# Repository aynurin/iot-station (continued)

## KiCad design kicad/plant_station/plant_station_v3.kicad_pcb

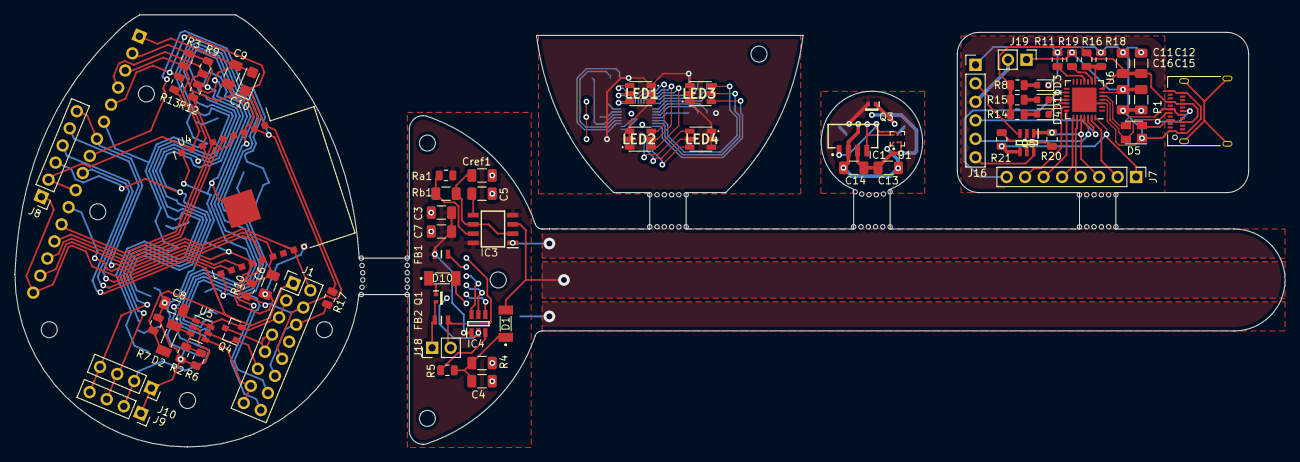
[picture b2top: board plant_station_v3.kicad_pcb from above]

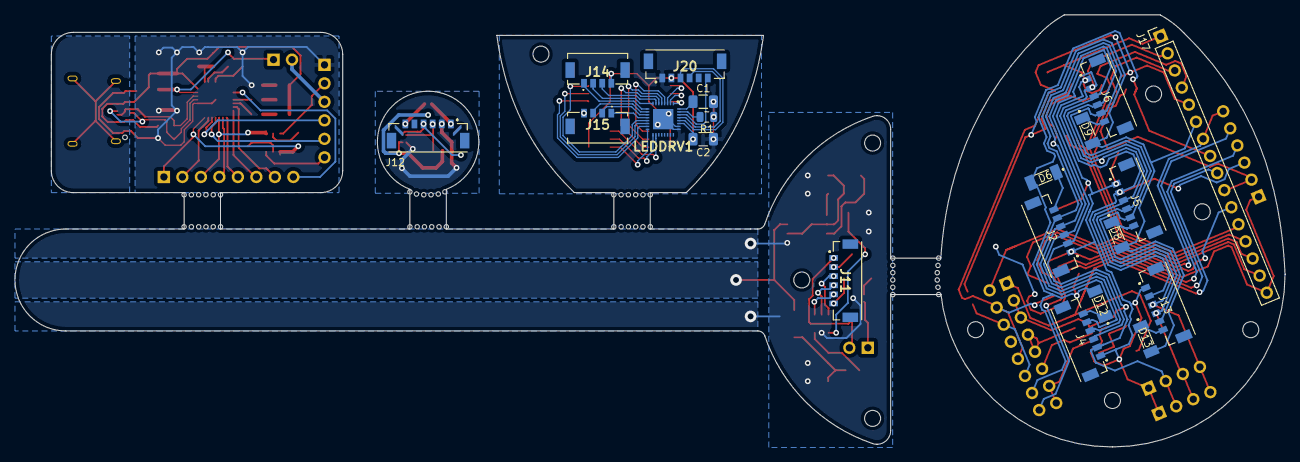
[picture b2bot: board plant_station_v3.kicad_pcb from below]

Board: 2 copper layers, 174.4 x 59.3 mm, 90 parts (20 on the bottom side), 95 nets.

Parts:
C1, C2, C4: 1μF; C_1206_3216Metric
C3, C6, C9, C11, C14, C15: 0.1μF; C_1206_3216Metric
C5: 10nF; C_1206_3216Metric
C7, C12, C13, C16: 4.7uF; C_1206_3216Metric
C8: 0.1uF; C_1206_3216Metric
C10: 220uF; CP_EIA-3216-18_Kemet-A
Cref1: 470pF; C_1206_3216Metric
D1, D2, D6, D8, D9, D10, D12, D13: LS4148; MELF_SOD_80_3_BZT55B13GS08
D3: 150060AS75000; LED_0603_1608Metric
D4: 150060BS75020; LED_0603_1608Metric
D5: SP0503BAHT; SOT-143
D11: 150060VS75000; LED_0603_1608Metric
FB1, FB2: BLM21AG601SZ1D; Ferrite_Bead_0805_BLM21
IC1: VEML7700-TT; VEML7700
IC3: TLC555CDR; SOIC127P600X175-8N
IC4: ADC081C021CIMK_NOPB; SOT95P280X110-6N
J1: Conn_02x08_Odd_Even; PinHeader_2x08_P2.54mm_Vertical
J2, J4, J5, J6, J13: MB_I2C; Molex_Conn_SMD_01x06_505567_0671
J7: Conn_01x08; PinHeader_1x08_P2.54mm_Vertical
J8: UART; PinHeader_1x06_P2.54mm_Vertical
J9: I2C SCREEN; PinSocket_1x04_P2.54mm_Vertical
J10: I2C HOST; PinSocket_1x04_P2.54mm_Vertical
J11: SOIL_I2C; Molex_Conn_SMD_01x06_505567_0671
J12: WEATHER_I2C; Molex_Conn_SMD_01x06_505567_0671
J14: Ambient_Led_6; Molex_Conn_SMD_01x04_505567_0471
J15: Ambient_Led_5; Molex_Conn_SMD_01x04_505567_0471
J16: Conn_01x06; PinHeader_1x06_P2.54mm_Vertical
J17: GPIO; PinHeader_1x16_P2.54mm_Vertical
J18: ALWAYS_ON; PinHeader_1x02_P2.54mm_Vertical
J19: Ammeter_Jumper; PinHeader_1x02_P2.54mm_Vertical
J20: LED_I2C; Molex_Conn_SMD_01x06_505567_0671
LED1, LED2, LED3, LED4: KRTBLSLPS1.32-VUVX-EQ+BTBV-D8+TWTZ-L1-B; KRTBLSLPS132VUVXEQBTBVD8TWTZL1B
LEDDRV1: LP5024RSMR; QFN40P400X400X100-33N-D
P1: USB_C_Plug_USB2.0; USB_C_Receptacle_Amphenol_12401610E4-2A
Q1, Q3: DTC113Z; DTC113ZEBTL
Q4: DMG2301L; SOT-23
Q5: BC817DS,115; SOT95P275X110-6N
R1: 4K9; R_0805_2012Metric
R2: 16.9K; R_0805_2012Metric
R3, R9: 4K7; R_0805_2012Metric
R4: 1M; R_1206_3216Metric
R5: 22; R_0805_2012Metric
R6: 97.6K; R_0805_2012Metric
R7, R10, R11, R12, R13, R17, R20, R21: 10K; R_0805_2012Metric
R8, R14, R15, R19: 1K; R_0805_2012Metric
R16: 22K1; R_0805_2012Metric
R18: 47K5; R_0805_2012Metric
Ra1: 330; R_0805_2012Metric
Rb1: 1K6; R_1206_3216Metric
U1: HDC2010YPAT; BGA6C100X50P2X3_146X146X67
U4: ESP-WROOM-02
U5: TPL5110; SOT-23-6
U6: CP2102N-A01-GQFN28; QFN-28-1EP_5x5mm_P0.5mm_EP3.35x3.35mm

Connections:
+3V3: C10.1, J1.4, J1.10, J17.5, R10.1, R13.1, U4.1
/ALL_EN: D6.2, D8.2, D9.2, D12.2, D13.2, J1.14, J17.6, U4.10
/HOST_WAKE: J2.5, J4.5, J5.5, J6.5, J13.5
/SCL: J2.4, J4.4, J5.4, J6.4, J9.3, J10.3, J13.4, J17.4, R9.2, U4.3
/SDA: J2.3, J4.3, J5.3, J6.3, J9.4, J10.4, J13.3, J17.3, R3.2, U4.7
/env_sensor/ALL_EN: J12.6, Q3.1
/env_sensor/GNDA: C13.2, C14.2, IC1.3, Q3.3, U1.B1, U1.C1
/env_sensor/SCL: IC1.1, J12.4, U1.B2
/env_sensor/SDA: IC1.4, J12.3, U1.A2
/esp8266/ESP_EN: C9.2, J17.8, R17.1, U4.2
/esp8266/ESP_RST: C6.2, J8.6, J17.7, R10.2, U4.15
/esp8266/GPIO0: J8.2, J17.10, R13.2, U4.8
/esp8266/GPIO5: J1.16, J17.11, U4.14
/esp8266/GPIO12: J17.14, U4.4
/esp8266/GPIO13: J17.13, U4.5
/esp8266/GPIO15: J17.12, R12.2, U4.6
/esp8266/GPIO16: J1.2, J17.15, U4.17
/esp8266/USB_RXD: J8.5, U4.12
/esp8266/USB_TXD: J8.4, U4.11
/esp8266/WAKE_UP: D2.2, J1.1, J17.9, R7.2
/leds/ALL_EN: J20.6, LEDDRV1.30
/leds/LED_1_B: LED1.C1, LEDDRV1.3
/leds/LED_1_G: LED1.C2, LEDDRV1.2
/leds/LED_1_R: LED1.C3, LEDDRV1.1
/leds/LED_2_B: LED2.C1, LEDDRV1.6
/leds/LED_2_G: LED2.C2, LEDDRV1.5
/leds/LED_2_R: LED2.C3, LEDDRV1.4
/leds/LED_3_B: J14.1, LEDDRV1.9
/leds/LED_3_G: J14.2, LEDDRV1.8
/leds/LED_3_R: J14.3, LEDDRV1.7
/leds/LED_4_B: J15.1, LEDDRV1.12
/leds/LED_4_G: J15.2, LEDDRV1.11
/leds/LED_4_R: J15.3, LEDDRV1.10
/leds/LED_5_B: LED3.C1, LEDDRV1.15
/leds/LED_5_G: LED3.C2, LEDDRV1.14
/leds/LED_5_R: LED3.C3, LEDDRV1.13
/leds/LED_6_B: LED4.C1, LEDDRV1.18
/leds/LED_6_G: LED4.C2, LEDDRV1.17
/leds/LED_6_R: LED4.C3, LEDDRV1.16
/leds/SCL: J20.4, LEDDRV1.29
/leds/SDA: J20.3, LEDDRV1.28
/moisture_sensor/ALL_EN: D10.2, J11.6
/moisture_sensor/GNDA: C3.1, C4.2, C5.2, C7.2, Cref1.2, IC3.1, IC4.2, Q1.3, R4.2
/moisture_sensor/HOST_WAKE: IC4.4, J11.5
/moisture_sensor/SCL: IC4.5, J11.4
/moisture_sensor/SDA: IC4.6, J11.3
/moisture_sensor/Sensor_Inside: D1.2, IC3.3
/moisture_sensor/VA: C3.2, C7.1, FB1.2, IC3.4, IC3.8, IC4.1, Ra1.1
/usb_serial/D+: D5.4, P1.A6, P1.B6, U6.4
/usb_serial/D-: D5.3, P1.A7, P1.B7, U6.5
/usb_serial/ESP_RST: J16.6, Q5.6
/usb_serial/GPIO0: J16.2, Q5.3
/usb_serial/USB_CTS: J7.4, U6.23
/usb_serial/USB_DSR: J7.2, U6.27
/usb_serial/USB_DTR: J7.1, Q5.4, R21.1, U6.28
/usb_serial/USB_GPIO.4: J7.5, U6.22
/usb_serial/USB_GPIO.5: J7.6, U6.21
/usb_serial/USB_GPIO.6: J7.7, U6.20
/usb_serial/USB_RTS: J7.3, Q5.1, R20.2, U6.24
/usb_serial/USB_RXD: J16.5, U6.25
/usb_serial/USB_RXT: D11.1, U6.18
/usb_serial/USB_TXD: J16.4, U6.26
/usb_serial/USB_TXT: D4.1, U6.19
/usb_serial/USB_WAKEUP: J7.8, U6.16
GND: C1.2, C2.1, C6.1, C8.1, C9.1, C10.2, C11.2, C12.1, C15.2, C16.1, D3.1, D5.1, FB2.2, J2.1, J4.1, J5.1, J6.1, J8.1, J9.1, J10.1, J11.1, J12.1, J13.1, J16.1, J17.1, J17.16, J18.2, J20.1, LEDDRV1.25, LEDDRV1.26, LEDDRV1.33, P1.A1, P1.A12, P1.B1, P1.B12, Q3.2, R1.1, R2.2, R6.2, R7.1, R11.2, R12.1, R18.2, U4.9, U4.13, U4.18, U4.19, U5.2, U6.3, U6.29
unnamed: C1.1, LEDDRV1.32
unnamed: C4.1, D1.1, R4.1, R5.2
unnamed: C5.1, IC3.5
unnamed: C11.1, C12.2, D5.2, P1.A4, P1.A9, P1.B4, P1.B9, R8.1, R14.1, R15.1, R16.2, U6.7
unnamed: C15.1, C16.2, J19.1, R19.1, U6.6
unnamed: Cref1.1, IC3.2, IC3.6, Rb1.2
unnamed: D2.1, R2.1, R6.1, U5.3
unnamed: D3.2, R8.2
unnamed: D4.2, R14.2
unnamed: D6.1, J2.6
unnamed: D8.1, J5.6
unnamed: D9.1, J6.6
unnamed: D10.1, Q1.1
unnamed: D11.2, R15.2
unnamed: D12.1, J4.6
unnamed: D13.1, J13.6
unnamed: FB2.1, J18.1, Q1.2
unnamed: IC3.7, Ra1.2, Rb1.1
unnamed: IC4.3, R5.1
unnamed: J1.7, J1.9, Q4.3
unnamed: J1.11, Q4.1, U5.5
unnamed: J1.6, J1.12, R17.2
unnamed: J1.13, J1.15, U5.4
unnamed: LEDDRV1.31, R1.2
unnamed: Q5.2, R21.2
unnamed: Q5.5, R20.1
unnamed: R11.1, U6.11
unnamed: R16.1, R18.1, U6.8
unnamed: R19.2, U6.9
VDD: C2.2, C8.2, C13.1, C14.1, FB1.1, IC1.2, J1.3, J1.5, J2.2, J4.2, J5.2, J6.2, J8.3, J9.2, J10.2, J11.2, J12.2, J13.2, J14.4, J15.4, J16.3, J17.2, J19.2, J20.2, LED1.A1, LED1.A2, LED1.A3, LED2.A1, LED2.A2, LED2.A3, LED3.A1, LED3.A2, LED3.A3, LED4.A1, LED4.A2, LED4.A3, LEDDRV1.27, Q4.2, R3.1, R9.1, U1.A1, U5.1, U5.6

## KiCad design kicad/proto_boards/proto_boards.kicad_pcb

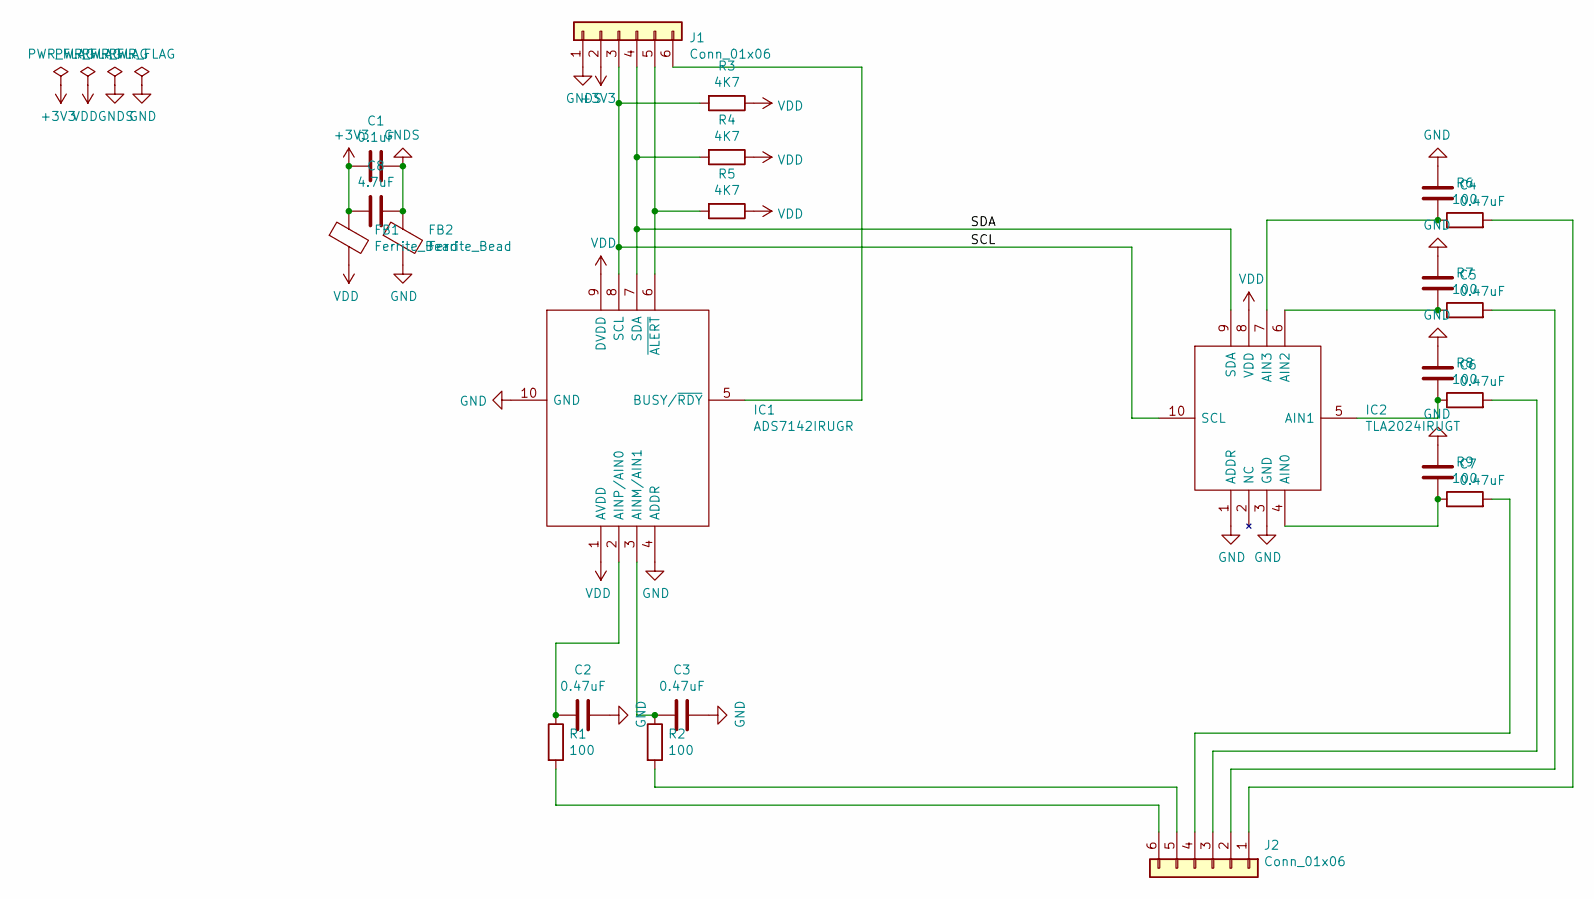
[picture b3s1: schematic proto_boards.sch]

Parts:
C1: 0.1uF; C_1206_3216Metric
C2, C3, C4, C5, C6, C7: 0.47uF; C_0805_2012Metric
C8: 4.7uF; C_1206_3216Metric
FB1, FB2: Ferrite_Bead; C_0805_2012Metric
IC1: ADS7142IRUGR; ADS1018IRUGT; Manufacturer_Part_Number ADS7142IRUGR; Mouser Part Number 595-ADS7142IRUGR
IC2: TLA2024IRUGT; ADS1018IRUGT; Manufacturer_Part_Number TLA2024IRUGT; Mouser Part Number 595-TLA2024IRUGT
J1, J2: Conn_01x06; PinHeader_1x06_P2.54mm_Vertical
R1, R2, R6, R7, R8, R9: 100; R_1206_3216Metric
R3, R4, R5: 4K7; R_0805_2012Metric

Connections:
+3V3: C1.2, C8.2, FB1.1, J1.2
/SCL: IC1.8 (SCL), IC2.10 (SCL), J1.3, R3.2
/SDA: IC1.7 (SDA), IC2.9 (SDA), J1.4, R4.2
GND: C2.1, C3.1, C4.1, C5.1, C6.1, C7.1, FB2.2, IC1.4 (ADDR), IC1.10 (GND), IC2.1 (ADDR), IC2.3 (GND)
GNDS: C1.1, C8.1, FB2.1, J1.1
unnamed: C2.2, IC1.2 (AINP/AIN0), R1.1
unnamed: C3.2, IC1.3 (AINM/AIN1), R2.1
unnamed: C4.2, IC2.7 (AIN3), R6.1
unnamed: C5.2, IC2.6 (AIN2), R7.1
unnamed: C6.2, IC2.5 (AIN1), R8.1
unnamed: C7.2, IC2.4 (AIN0), R9.1
unnamed: IC1.5 (BUSY/~RDY), J1.6
unnamed: IC1.6 (~ALERT), J1.5, R5.2
unnamed: J2.1, R6.2
unnamed: J2.2, R7.2
unnamed: J2.3, R8.2
unnamed: J2.4, R9.2
unnamed: J2.5, R2.2
unnamed: J2.6, R1.2
VDD: FB1.2, IC1.1 (AVDD), IC1.9 (DVDD), IC2.8 (VDD), R3.1, R4.1, R5.1

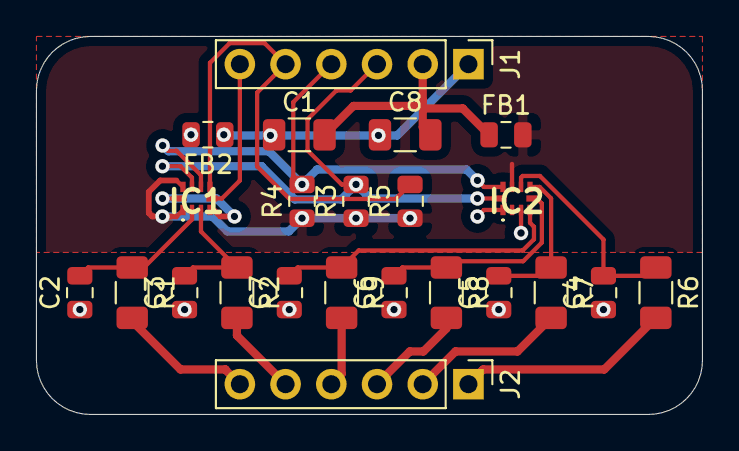
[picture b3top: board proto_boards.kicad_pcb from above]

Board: 2 copper layers, 37.0 x 21.0 mm, 23 parts (0 on the bottom side), 20 nets.

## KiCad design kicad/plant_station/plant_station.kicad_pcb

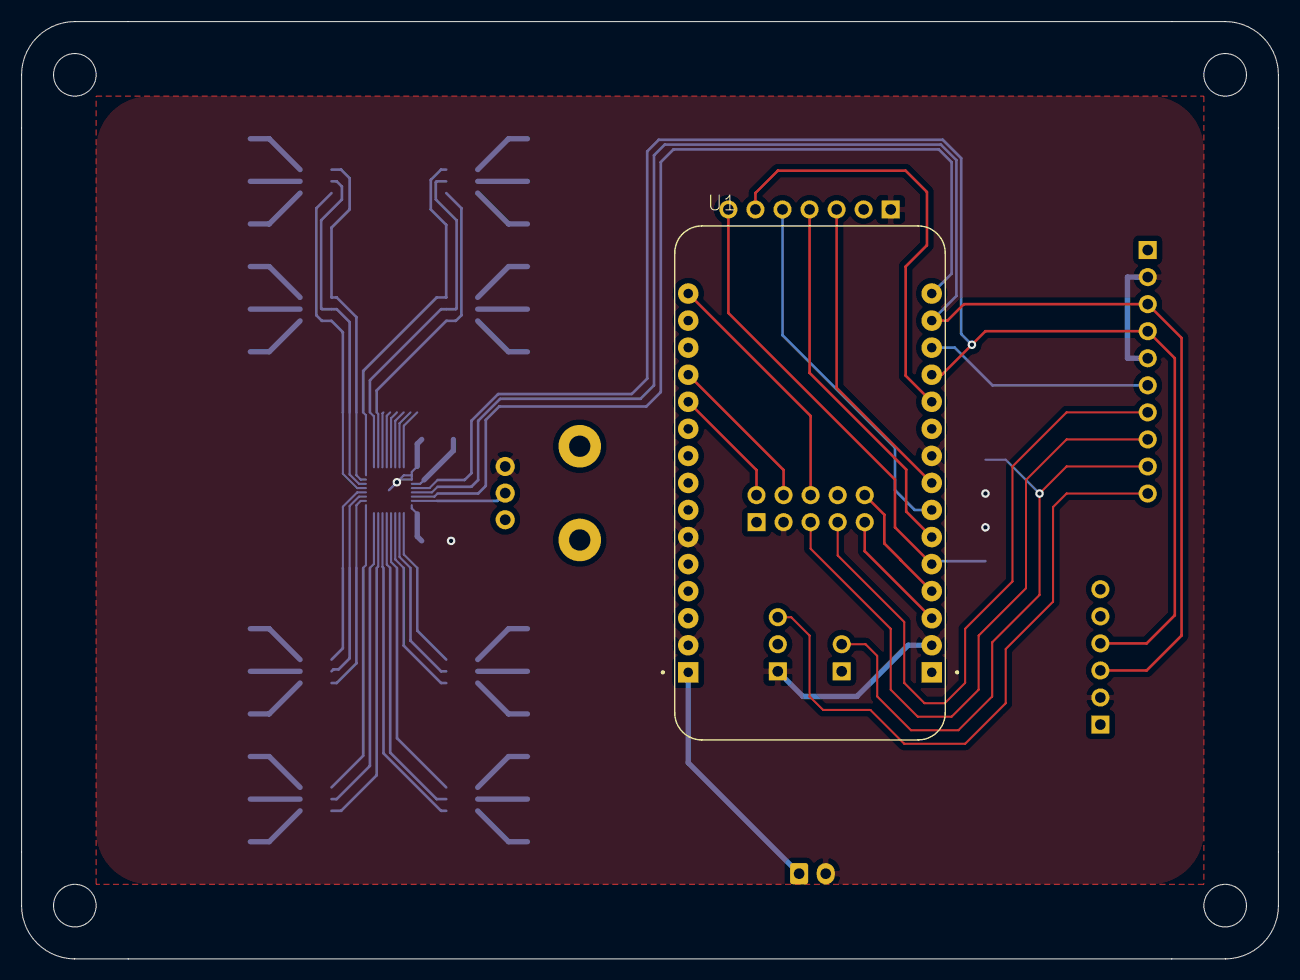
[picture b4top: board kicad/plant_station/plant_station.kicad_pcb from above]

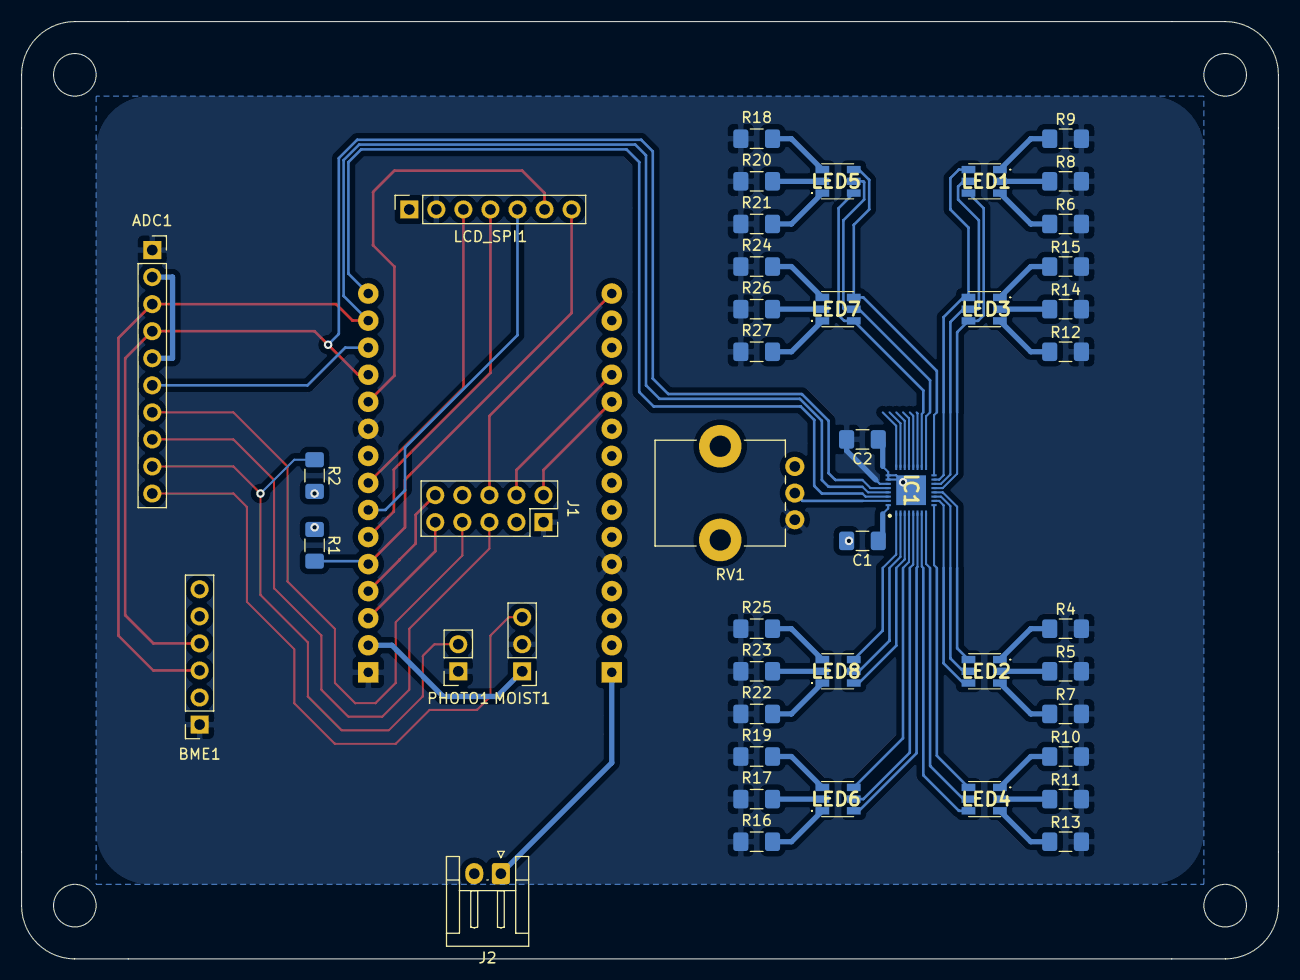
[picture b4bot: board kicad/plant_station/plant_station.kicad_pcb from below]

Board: 2 copper layers, 118.0 x 88.0 mm, 46 parts (45 on the bottom side), 65 nets.

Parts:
ADC1: ADS1115; PinSocket_1x10_P2.54mm_Vertical
BME1: BME280; PinSocket_1x06_P2.54mm_Vertical
C1, C2: 1μF; C_1206_3216Metric_Pad1.42x1.75mm_HandSolder
IC1: LP5024RSMR; QFN40P400X400X100-33N-D
J1: Conn_02x05_Odd_Even; PinSocket_2x05_P2.54mm_Vertical
J2: Conn_01x02_Female; JST_EH_S2B-EH_1x02_P2.50mm_Horizontal
LCD_SPI1: SSD1306SPI; PinSocket_1x07_P2.54mm_Vertical
LED1, LED2, LED3, LED4, LED5, LED6, LED7, LED8: LED; KRTBLSLPS132VUVXEQBTBVD8TWTZL1B
MOIST1: MOIST; PinHeader_1x03_P2.54mm_Vertical
PHOTO1: R_PHOTO; PinSocket_1x02_P2.54mm_Vertical
R1, R2: 10K; R_1206_3216Metric_Pad1.42x1.75mm_HandSolder
R4, R5, R8, R9, R10, R11, R14, R15, R16, R17, R20, R21, R22, R23, R26, R27: 47; R_1206_3216Metric_Pad1.42x1.75mm_HandSolder
R6, R7, R12, R13, R18, R19, R24, R25: 100; R_1206_3216Metric_Pad1.42x1.75mm_HandSolder
RV1: R_POT 5K (for 15mA LED); Potentiometer_Bourns_PTV09A-1_Single_Vertical
U1: NodeMCU2; NodeMCU

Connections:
+3V3: ADC1.1, BME1.1, C2.2, IC1.27, J1.1, LCD_SPI1.2, MOIST1.2, PHOTO1.1, R4.2, R5.2, R6.2, R7.2, R8.2, R9.2, R10.2, R11.2, R12.2, R13.2, R14.2, R15.2, R16.2, R17.2, R18.2, R19.2, R20.2, R21.2, R22.2, R23.2, R24.2, R25.2, R26.2, R27.2, RV1.3, U1.3V3
+5V: J2.1, U1.Vin
GND: ADC1.2, ADC1.5, BME1.2, C1.2, C2.1, IC1.25, IC1.26, IC1.33, J1.3, J2.2, LCD_SPI1.1, MOIST1.1, R1.1, R2.2, RV1.1, U1.GND
unnamed: ADC1.3, BME1.3, IC1.29, U1.D1
unnamed: ADC1.4, BME1.4, IC1.28, U1.D3
unnamed: ADC1.6, U1.D2
unnamed: ADC1.7, J1.7
unnamed: ADC1.8, J1.5
unnamed: ADC1.9, PHOTO1.2, R2.1
unnamed: ADC1.10, MOIST1.3
unnamed: C1.1, IC1.32
unnamed: IC1.1, LED8.C3
unnamed: IC1.2, LED8.C2
unnamed: IC1.3, LED8.C1
unnamed: IC1.4, LED6.C3
unnamed: IC1.5, LED6.C2
unnamed: IC1.6, LED6.C1
unnamed: IC1.7, LED4.C3
unnamed: IC1.8, LED4.C2
unnamed: IC1.9, LED4.C1
unnamed: IC1.10, LED2.C3
unnamed: IC1.11, LED2.C2
unnamed: IC1.12, LED2.C1
unnamed: IC1.13, LED1.C3, LED3.C3
unnamed: IC1.14, LED1.C2, LED3.C2
unnamed: IC1.15, LED1.C1, LED3.C1
unnamed: IC1.16, LED5.C3, LED7.C3
unnamed: IC1.17, LED5.C2, LED7.C2
unnamed: IC1.18, LED5.C1, LED7.C1
unnamed: IC1.30, U1.D0
unnamed: IC1.31, RV1.2
unnamed: J1.2, U1.SD2
unnamed: J1.4, U1.SD3
unnamed: J1.6, U1.A0
unnamed: J1.9, U1.D10
unnamed: J1.10, U1.D9
unnamed: LCD_SPI1.3, U1.D5
unnamed: LCD_SPI1.4, U1.D7
unnamed: LCD_SPI1.5, U1.D6
unnamed: LCD_SPI1.6, U1.D4
unnamed: LCD_SPI1.7, R1.2, U1.D8
unnamed: LED1.A1, R9.1
unnamed: LED1.A2, R8.1
unnamed: LED1.A3, R6.1
unnamed: LED2.A1, R4.1
unnamed: LED2.A2, R5.1
unnamed: LED2.A3, R7.1
unnamed: LED3.A1, R15.1
unnamed: LED3.A2, R14.1
unnamed: LED3.A3, R12.1
unnamed: LED4.A1, R10.1
unnamed: LED4.A2, R11.1
unnamed: LED4.A3, R13.1
unnamed: LED5.A1, R21.1
unnamed: LED5.A2, R20.1
unnamed: LED5.A3, R18.1
unnamed: LED6.A1, R16.1
unnamed: LED6.A2, R17.1
unnamed: LED6.A3, R19.1
unnamed: LED7.A1, R27.1
unnamed: LED7.A2, R26.1
unnamed: LED7.A3, R24.1
unnamed: LED8.A1, R22.1
unnamed: LED8.A2, R23.1
unnamed: LED8.A3, R25.1

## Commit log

2020-05-23 CCS811 wired and reading
2020-05-25 Sending data to Azure
2020-06-03 Initial refactoring to organize code
2020-06-04 Remapped I2C pins to D3 and D1 to release a PWM pin
2020-06-07 Soil moisture sensor
2020-06-15 KiCad draft
2020-06-16 Added GND and 3V3 areas and tracks to connect NodeMCU
2020-06-19 PCB 0.1 sent to production
2020-07-03 Scheme v.2 wired up
2020-07-10 Board v.2 sent for printing
2020-07-28 Started working on v3 - added ADC081 driver and removed CAP and IQS chips
2020-08-12 v3 schematics complete, USB breakout PCB designed
2020-08-12 v3 PCB in progress. Need to move LED driver to LEDs board and make it connect using the standard interface
2020-08-13 Moved the LED driver to LEDs board, refactored connectors. Hopefuly PCBNEW could update it all in place
2020-08-14 LEDs board done via I2C bus
2020-08-18 Initial board layout complete
2020-08-30 pcb v3 sent to production and the first attempts to design the enclosure
2021-07-11 Pre-refactoring, diagnostics complete, timer not working properly
2021-07-24 project folder cleanup
2021-07-24 Roadmap
2021-07-24 Added Roadmap to README
2021-07-24 Create LICENSE
2021-07-24 Added licensing info
2021-07-24 Added milestone links
2021-07-24 USB Wiring updated to fix RSTb pull-up
2021-07-24 Added USB Charger Detection Specification (BCv1.2_070312)
2021-07-25 SPX3819 resistance calculator
2021-07-25 SPX3819 datasheet
2021-07-30 Libraries cleanup
2021-08-01 Charger initial wiring complete
2021-08-01 Schematics cleanup
2021-08-02 Comitting yesterday's leftovers
2021-08-03 Relabeled and completed ERC
2021-10-04 Mapped footprints, PCB in progress
2021-10-29 trying github dot
